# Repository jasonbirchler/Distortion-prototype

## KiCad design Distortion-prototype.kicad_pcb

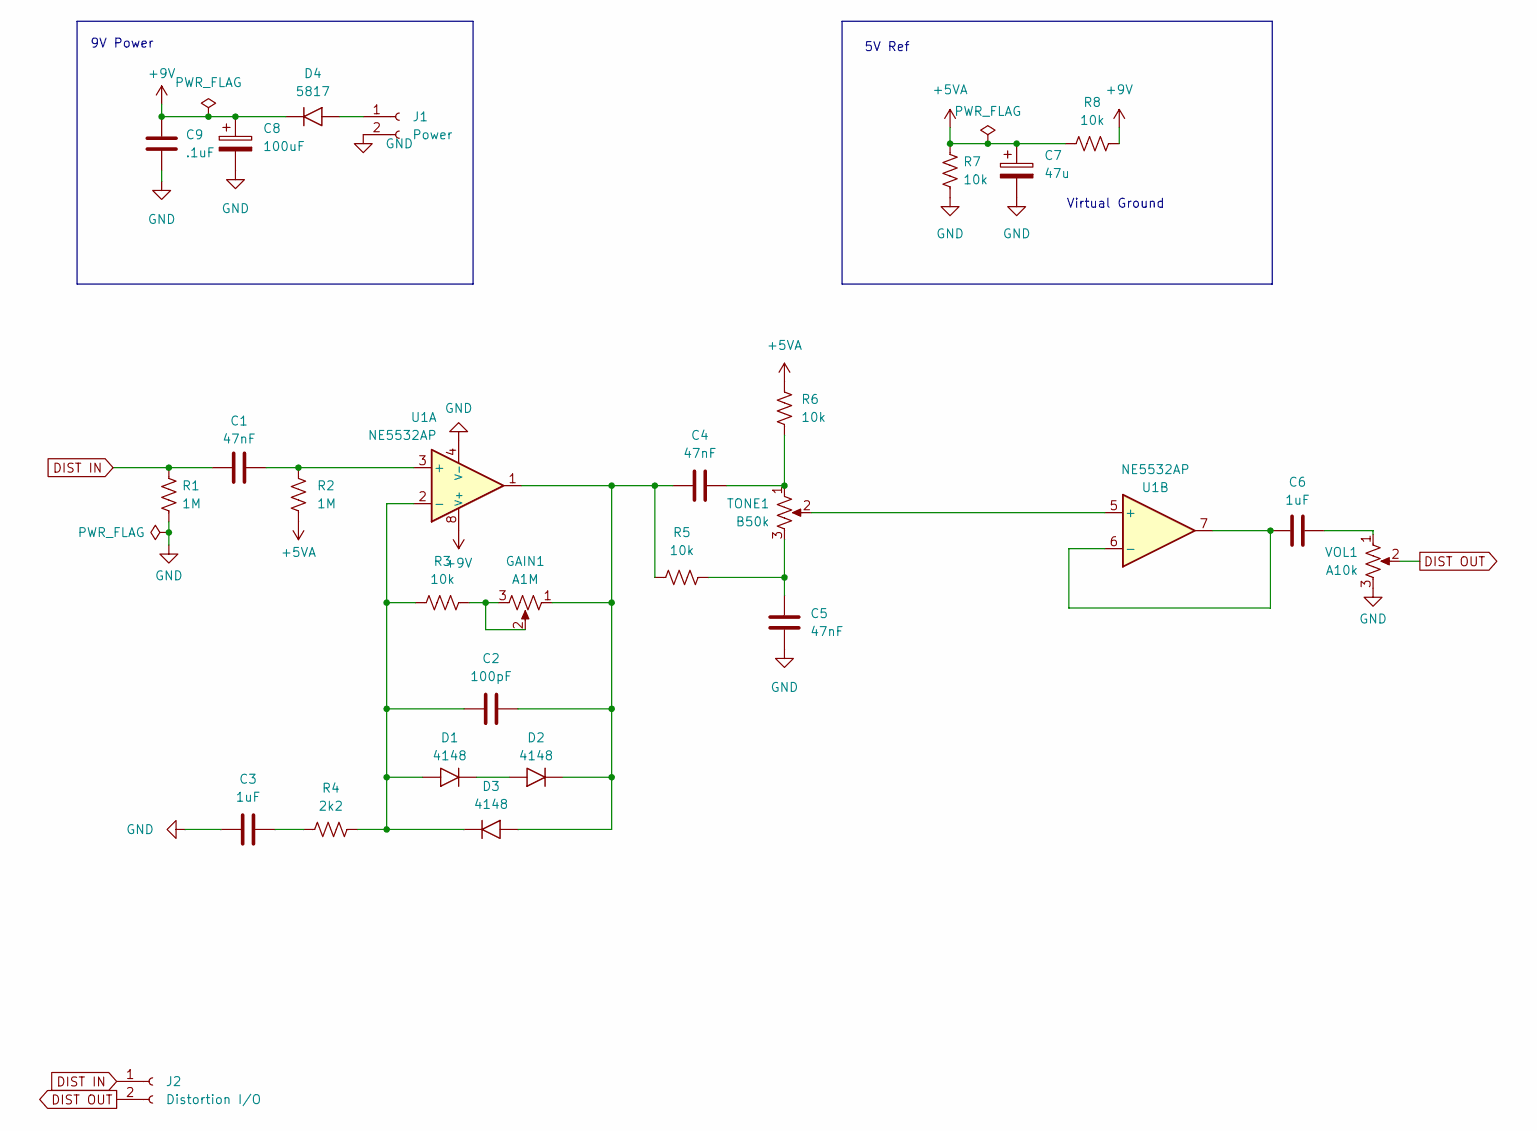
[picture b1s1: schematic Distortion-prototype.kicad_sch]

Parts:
C1, C4, C5: 47nF; C_Disc_D3.0mm_W1.6mm_P2.50mm
C2: 100pF; C_Disc_D3.0mm_W1.6mm_P2.50mm
C3, C6: 1uF; C_Disc_D3.0mm_W1.6mm_P2.50mm
C7: 47u; CP_Radial_D5.0mm_P2.50mm
C8: 100uF; CP_Radial_D5.0mm_P2.50mm
C9: .1uF; C_Disc_D3.0mm_W1.6mm_P2.50mm
D1, D2, D3: 4148; D_DO-34_SOD68_P7.62mm_Horizontal
D4: 5817; D_A-405_P7.62mm_Horizontal
GAIN1: A1M; PinHeader_1x03_P2.54mm_Vertical
J1: Power; PinSocket_2x01_P2.54mm_Vertical
J2: Distortion I/O; PinSocket_2x01_P2.54mm_Vertical
R1, R2: 1M; R_Axial_DIN0204_L3.6mm_D1.6mm_P7.62mm_Horizontal
R3, R5, R6, R7, R8: 10k; R_Axial_DIN0204_L3.6mm_D1.6mm_P7.62mm_Horizontal
R4: 2k2; R_Axial_DIN0204_L3.6mm_D1.6mm_P7.62mm_Horizontal
TONE1: B50k; PinHeader_1x03_P2.54mm_Vertical
U1: NE5532AP; DIP-8pin_TH
VOL1: A10k; PinHeader_1x03_P2.54mm_Vertical

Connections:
+5VA: C7.1, R2.2, R6.2, R7.1, R8.1
+9V: C8.1, C9.1, D4.1 (K), R8.2, U1.8 (V+)
DIST IN: C1.1, J2.1, R1.1
DIST OUT: J2.2, VOL1.2
GND: C3.1, C5.1, C7.2, C8.2, C9.2, J1.2, R1.2, R7.2, U1.4 (V-), VOL1.3
unnamed: C3.2, R4.1
unnamed: C4.2, R6.1, TONE1.1
unnamed: C5.2, R5.2, TONE1.3
unnamed: C6.1, VOL1.1
unnamed: C2.1, D1.2 (A), D3.1 (K), R3.1, R4.2, U1.2 (-)
unnamed: D1.1 (K), D2.2 (A)
unnamed: C2.2, C4.1, D2.1 (K), D3.2 (A), GAIN1.1, R5.1, U1.1
unnamed: D4.2 (A), J1.1
unnamed: GAIN1.2, GAIN1.3, R3.2
unnamed: C1.2, R2.1, U1.3 (+)
unnamed: TONE1.2, U1.5 (+)
unnamed: C6.2, U1.6 (-), U1.7

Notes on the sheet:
9V Power
Virtual Ground
5V Ref

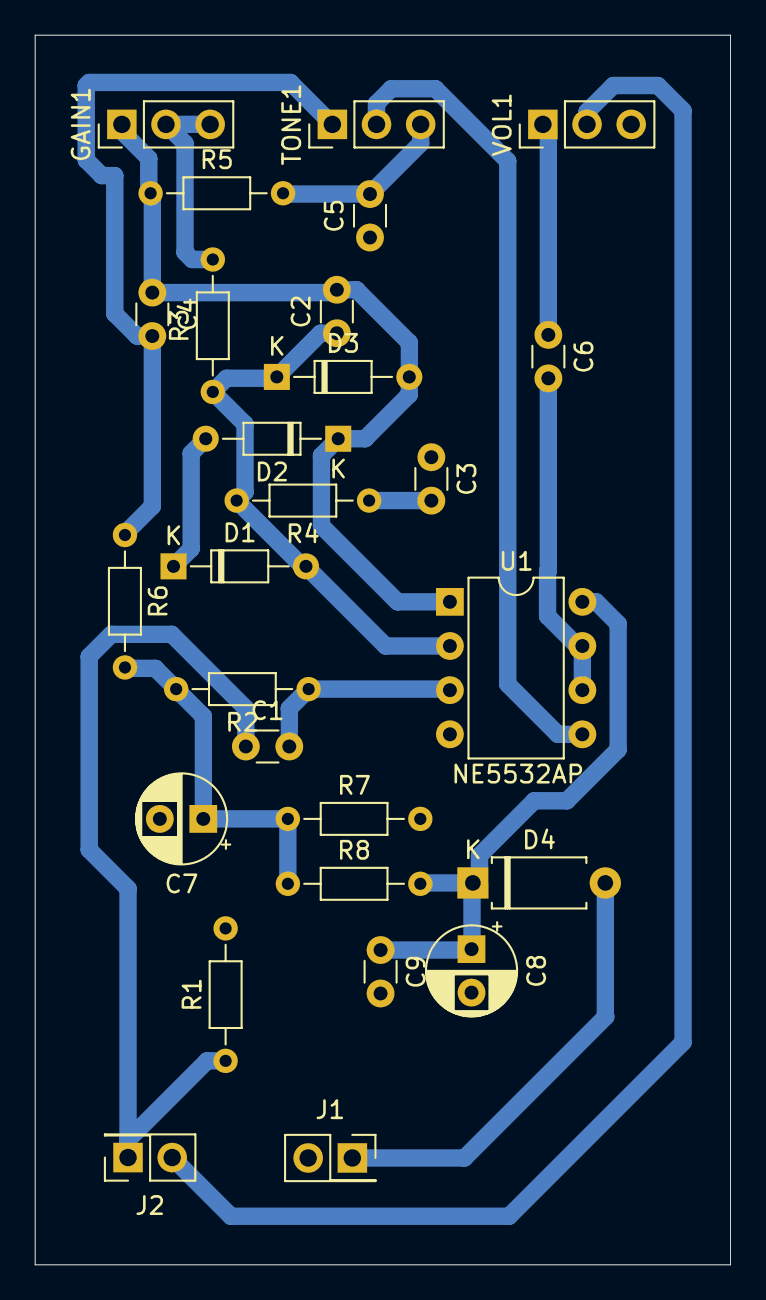
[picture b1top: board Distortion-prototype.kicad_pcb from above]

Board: 2 copper layers, 40.0 x 70.7 mm, 27 parts (0 on the bottom side), 17 nets.

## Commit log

2025-03-29 adds CAM outputs
